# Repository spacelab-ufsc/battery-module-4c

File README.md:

<h1 align="center">
	BATTERY MODULE 4 CELLS
	<br>
</h1>

<h4 align="center">Electrical power system battery module 4 cells hardware project (sources, outputs, and documentation).</h4>

<p align="center">

</p>

<p align="center">
  	<a href="#overview">Overview</a> •
  	<a href="#architecture">Architecture</a> •
  	<a href="#interface">Interface</a> •
  	<a href="#version">Version</a> •
  	<a href="#license">License</a> •
  	<a href="#notes">Notes</a>
</p>

## Overview

## Architecture

## Interface

## Version

The current version of the project is v0.1, the status is ```development```.

## License

This project is licensed under CERN Open Hardware License, version 2.

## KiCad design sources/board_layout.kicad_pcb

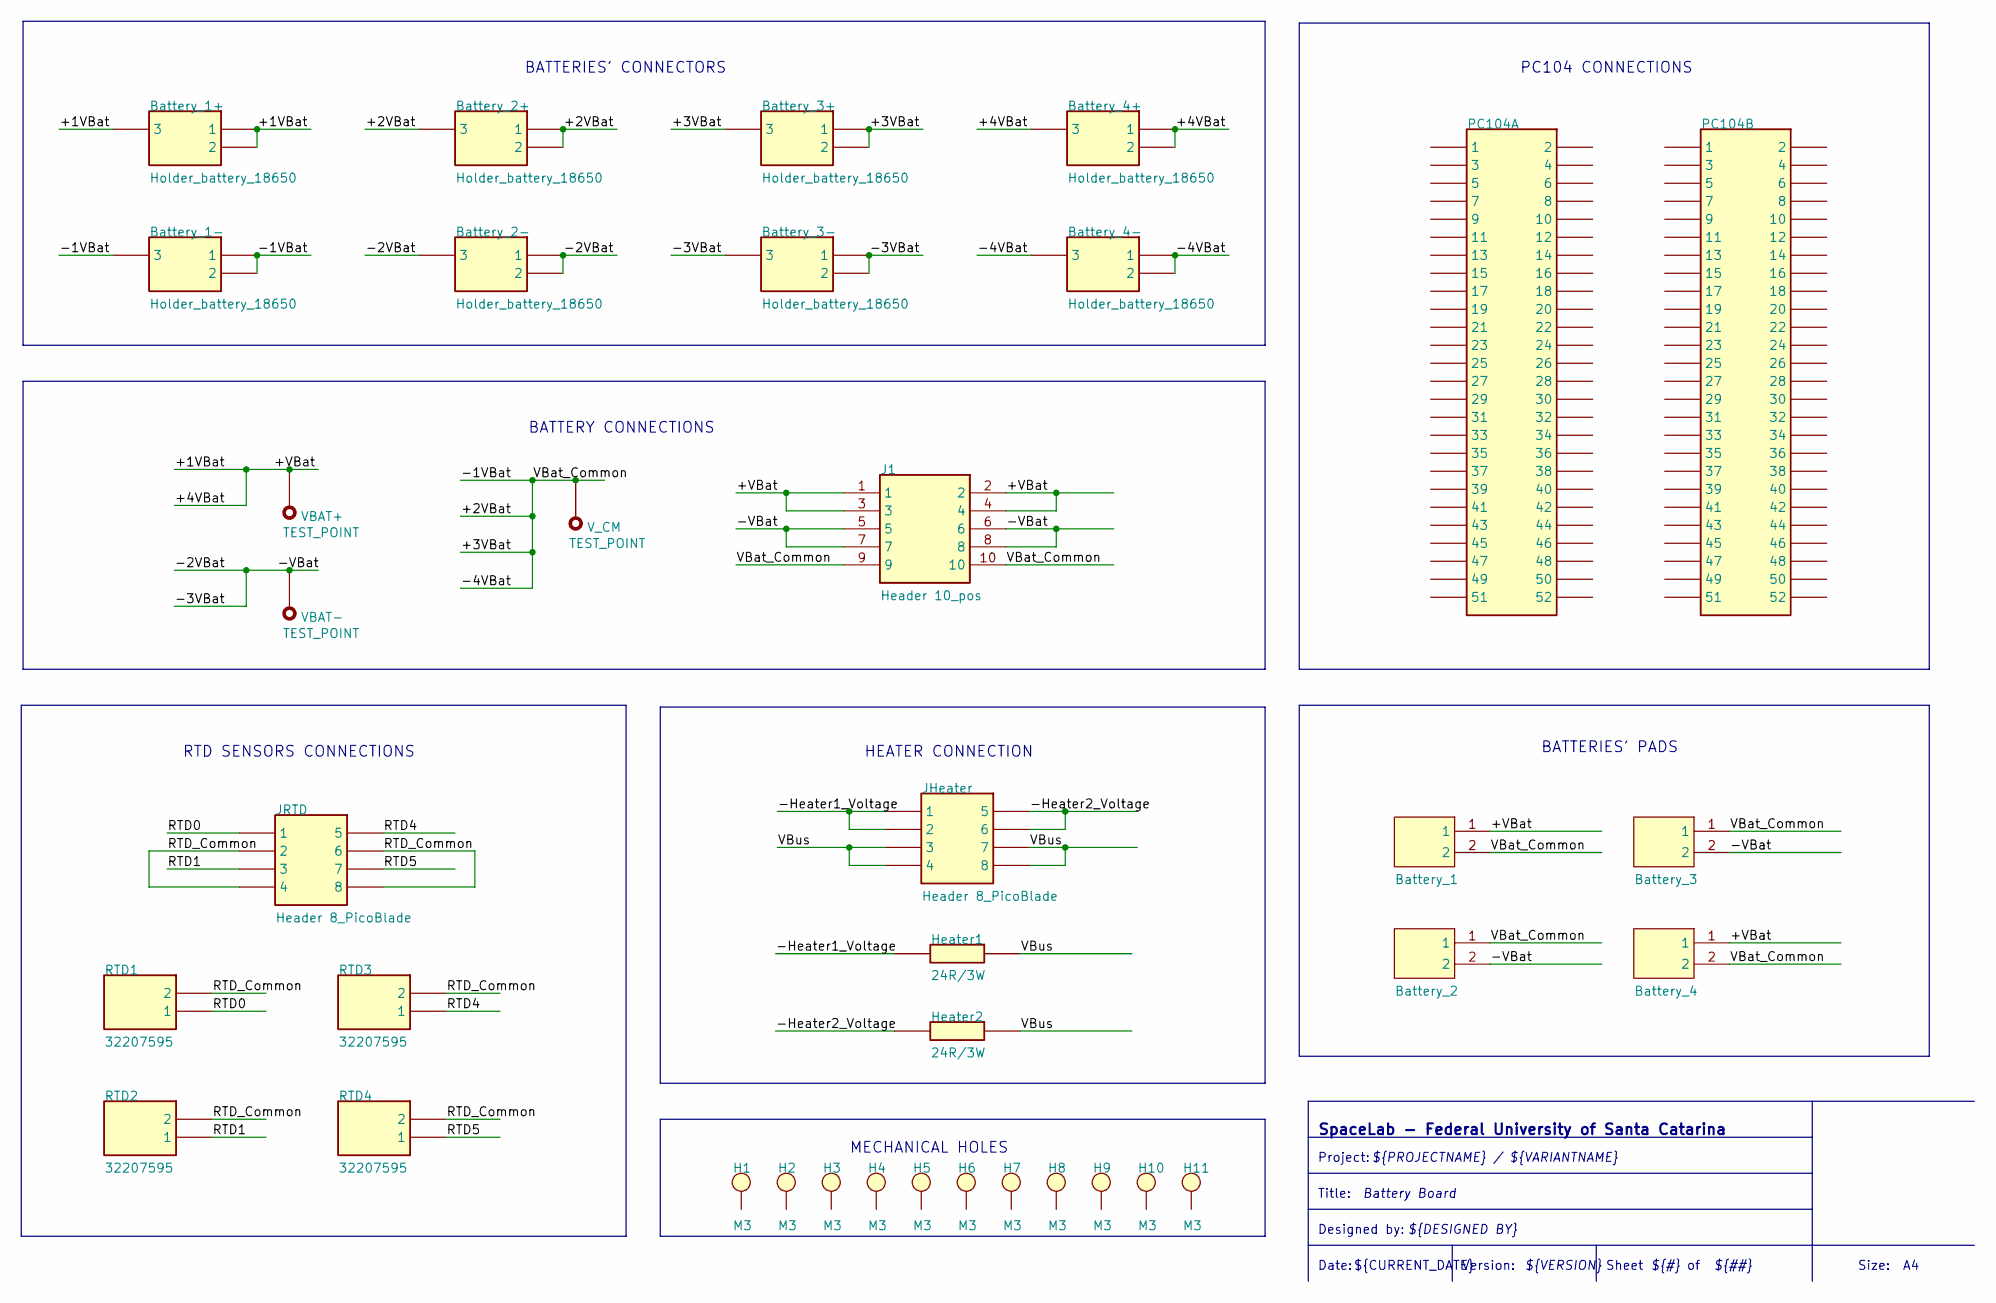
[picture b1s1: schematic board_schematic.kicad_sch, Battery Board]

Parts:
Battery_1, Battery_2, Battery_3, Battery_4: BATTERY
Battery_1+, Battery_1-, Battery_2+, Battery_2-, Battery_3+, Battery_3-, Battery_4+, Battery_4-: Holder_battery_18650; 54; MANUFACTURER_PART_NUMBER 54; MOUSER PART NUMBER 534-54
H1, H2, H3, H4, H5, H6, H7, H8, H9, H10, H11: M3; M3 hole
Heater1, Heater2: 24R/3W; RESAD3322W86L1422D475; MANUFACTURER_PART_NUMBER RS02B24R00FE12
J1: Header 10_pos; _Users_User_Desktop_Backup F__2020_Personal GitKraken_batte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; MANUFACTURER_PART_NUMBER 67996-110HLF; MOUSER PART NUMBER 649-67996-110HLF
JHeater: Header 8_PicoBlade; 53398-0871; MOUSER2 PART NUMBER 538-53398-0871
JRTD: Header 8_PicoBlade; 53398-0871; MOUSER2 PART NUMBER 538-53398-0871
PC104A, PC104B: ESQ-126-39-G-D; ESQ-126-Y-X-D; MANUFACTURER_PART_NUMBER ESQ-126-39-G-D; MOUSER PART NUMBER 200-ESQ12639GD
RTD1, RTD2, RTD3, RTD4: 32207595; THRMC3216X70N; MANUFACTURER_PART_NUMBER 32207595
VBAT+: TEST_POINT; Test_Point
VBAT-: TEST_POINT; Test_Point
V_CM: TEST_POINT; Test_Point

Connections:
+1VBat: Battery_1.1, Battery_1+.1, Battery_1+.2, Battery_1+.3, Battery_4.1, Battery_4+.1, Battery_4+.2, Battery_4+.3, J1.1, J1.2, J1.3, J1.4, VBAT+.1
+2VBat: Battery_1.2, Battery_1-.1, Battery_1-.2, Battery_1-.3, Battery_2.1, Battery_2+.1, Battery_2+.2, Battery_2+.3, Battery_3.1, Battery_3+.1, Battery_3+.2, Battery_3+.3, Battery_4.2, Battery_4-.1, Battery_4-.2, Battery_4-.3, J1.9, J1.10, V_CM.1
-2VBat: Battery_2.2, Battery_2-.1, Battery_2-.2, Battery_2-.3, Battery_3.2, Battery_3-.1, Battery_3-.2, Battery_3-.3, J1.5, J1.6, J1.7, J1.8, VBAT-.1
-Heater1_Voltage: Heater1.1, JHeater.1, JHeater.2
-Heater2_Voltage: Heater2.1, JHeater.5, JHeater.6
RTD0: JRTD.1, RTD1.1
RTD1: JRTD.3, RTD2.1
RTD4: JRTD.5, RTD3.1
RTD5: JRTD.7, RTD4.1
RTD_Common: JRTD.2, JRTD.4, JRTD.6, JRTD.8, RTD1.2, RTD2.2, RTD3.2, RTD4.2
VBus: Heater1.2, Heater2.2, JHeater.3, JHeater.4, JHeater.7, JHeater.8

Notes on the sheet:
SpaceLab - Federal University of Santa Catarina
BATTERIES' PADS
Size:
${CURRENT_DATE}
${##}
${DESIGNED BY}
${TITLE}
RTD SENSORS CONNECTIONS
BATTERIES' CONNECTORS
${PROJECTNAME} / ${VARIANTNAME}
BATTERY CONNECTIONS
Designed by:
Title:
PC104 CONNECTIONS
Version:
HEATER CONNECTION
${VERSION}
MECHANICAL HOLES
Date:
Project:
Sheet
${#}

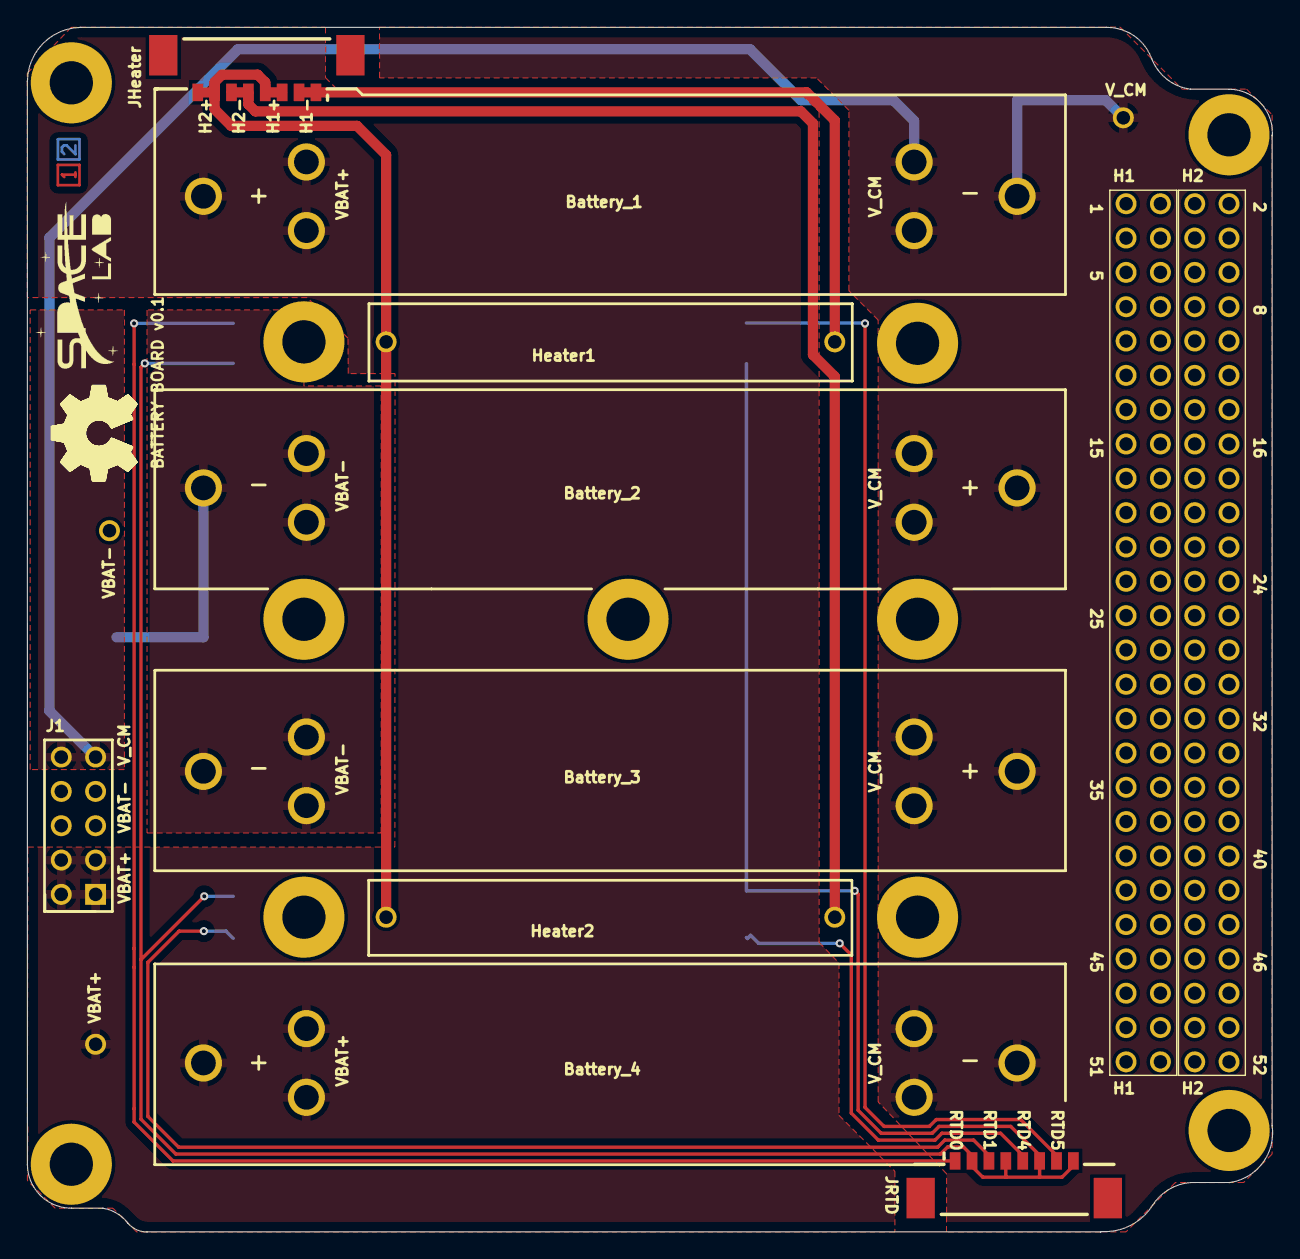
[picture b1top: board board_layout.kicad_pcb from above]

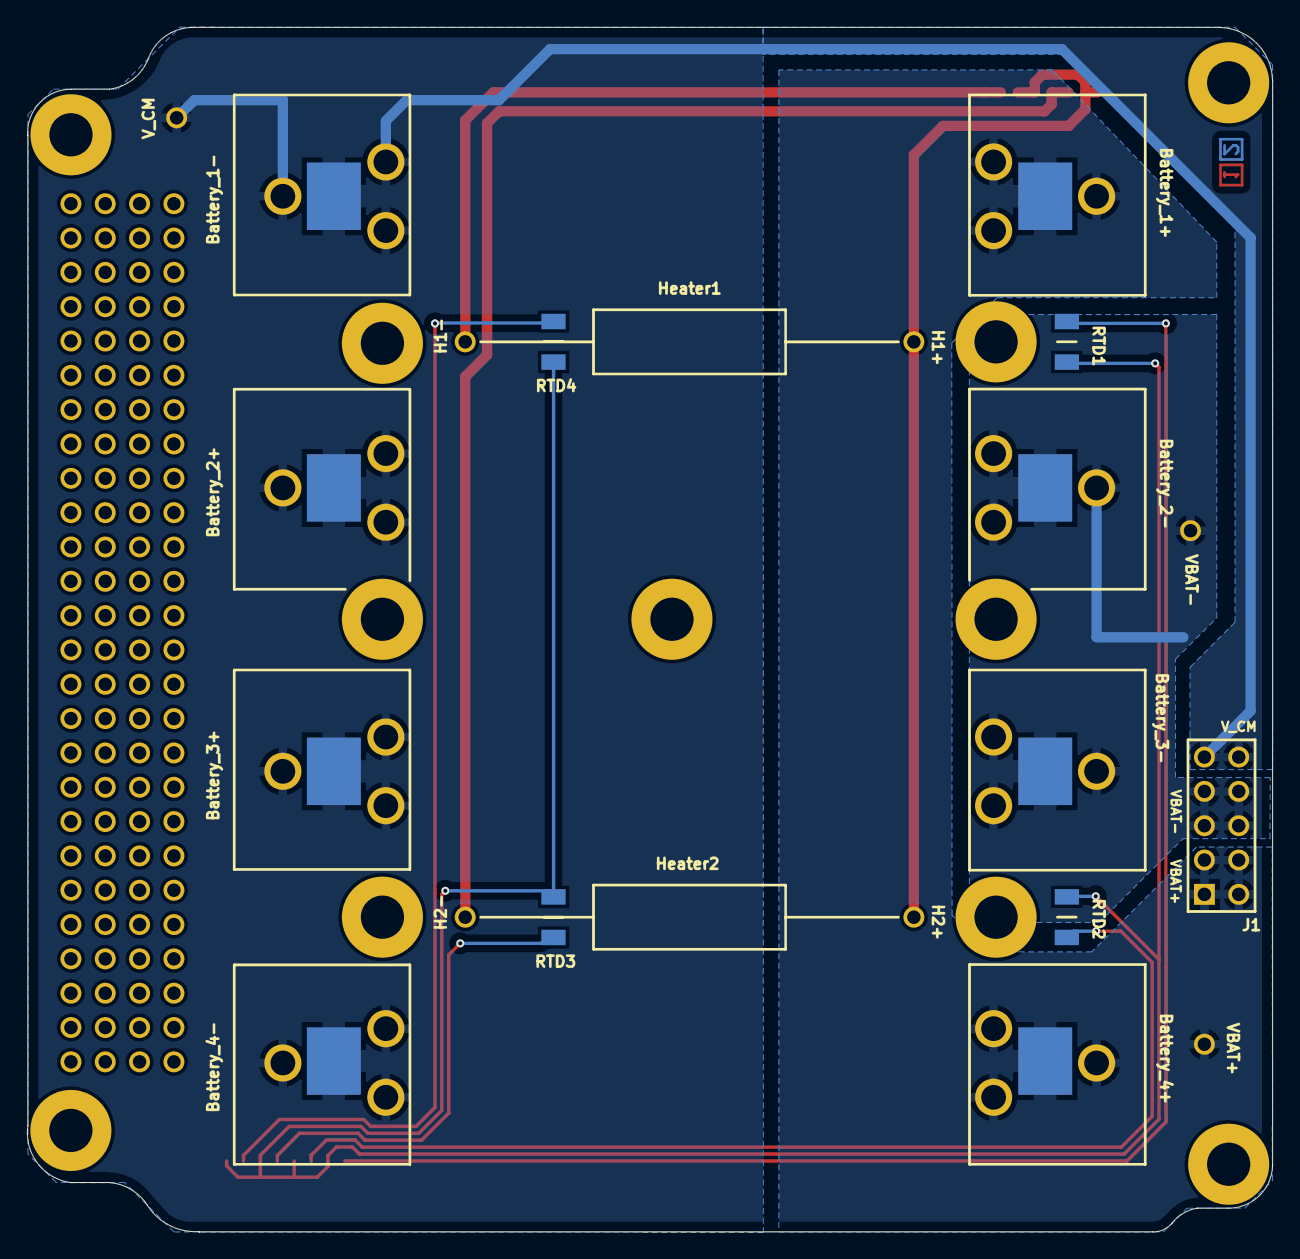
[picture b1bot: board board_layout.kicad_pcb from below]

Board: 2 copper layers, 92.1 x 89.1 mm, 37 parts (18 on the bottom side), 11 nets.

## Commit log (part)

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2020-05-06 hardware: Adding working files #1
2020-05-07 hardware: adding preliminary board shape and holes #2
2020-05-18 hardware: deleting resistors, adding step files, placing components #3
    Deleting resistors for replacement; additional step files of batteries, battery clips, preliminary resistors, PC104 connectors; placing first positioning of batteries, clips, sensors and resistors.
2020-05-27 hardware: replacing connectors and components, organizing files #4
    changing placement layers of picoblades, sensors, heaters and battery connectors; changing project files because of an minor error
2020-05-27 hardware: adding preliminary battery nets #5
    adding battery connectors polygon nets for posterior connection
2020-05-27 hardware: re-ranging heater's picoblade connections #6
    re-ranging net names for the heater's picoblade for compatibility with EPS board
2020-05-27 hardware: adding heater nets #8
2020-05-27 hardware: changing RTD's pins, removing pin numbers #7
    - rearranging RTD's picoblade pins for interface with EPS;
    - removing unnecessary information in the schematics.
2020-05-27 hardware: editing battery nets, changing sensors positions #9
    - connecting the battery clips nets to the J1 connector (EPS power connector);
    - removing sensors positions for future decision of them;
2020-05-27 hardware: arranging sensors positions, adding battery pads reference #10
    - placing new positions for the sensors, which was only possible by changing some of the battery nets;
    - adding a reference for future battery pads if the connectors aren't needed
2020-05-28 hardware: changing RTD's positions, connecting nets #11
    - changing RTD 2 and 4 position for better placement of the nets;
    - connecting the nets onto the RTD's picoblade.
2020-06-02 hardware: editing and replacing nets and vias #12
    - changes in heater's nets width and placement
    - changes in the rtd's nets and vias width
    - replacing rtd's nets for better positioning
2020-06-21 hardware: adding libraries and creating testpoint #13
    - creating a schematic and a PCB library
    - creating a testpoint symbol for the schematic
    - adding the testpoint footprint
2020-06-21 hardware: changing connections in the sheet #14
    - changing connectors' wires for better visualization
2020-06-21 hardware: adding testpoints to the sheet #15
    - placing the testpoints in the power connections
2020-06-21 hardware: netting testpoints #17
2020-06-21 hardware: adding and placing testpoints in the PCB #16
    - updating sheet connections to the PCB
    - placing testpoints far from battery clips, but near original nets
2020-06-24 hardware: creating battery direct pads #18
2020-06-24 hardware: creating battery's schematic symbol #19
2020-06-24 hardware: adding the new battery symbols to the schematic #20
2020-06-24 hardware: updating battery's files #21
2020-06-25 hardware: updating battery symbols to the schematic #22
2020-06-25 hardware: placing battery pads into the PCB #23
2020-06-27 hardware: editing polygon connections #24
2020-06-27 hardware: rearranging silkscreen #25
2020-06-27 hardware: minor silkscreen updates #26
2020-06-28 hardware: placing drill holes #27
2020-06-28 Ignoring all preview files from the project
2020-06-28 hardware: adding logo and board's name #28
    - minor labeling changes
    - adding FloripaSat's logo and board's name to the PCB project
    - final version of V2.0
2020-06-28 hardware: updating list of components on the libraries #29
2020-06-28 documentation: updating template's patch #2
2020-06-28 documentation: updating patch's placement #3
2020-07-02 hardware: updating schematics #30
    - deleting different common paths and combining them to a single one
2020-07-02 hardware: updating PCB after schematic changes #31
    - connecting all commons and deleting extra testpoint
    - aligning drill holes
2020-07-02 hardware: updating silkscreen #32
2020-07-11 documentation: updating patch's placement #4
    obs: after merge, update patch's location on the project
2020-07-11 documentation: creating pdf file for schematic #5
2020-08-17 hardware: minor changes in the silkscreen, adding GOLDS patch #32
    Also minor changes in the schematic template.
2020-08-18 documentation: updating schematics' pdf and adding project's BOM #6
    - rewriting component descriptions and names
    - adding an excel file with list of components
    - adding a pdf file of the same list
2020-08-18 hardware: updating project, adding used 3D step files #34
    - minor changes such as linking the footprints to the libraries
    - adding battery, battery clips and PC104 step files
2020-08-18 hardware: adding gerbers and drill files #35
2020-09-15 Fabrication: Generating preliminary fabrication files
2020-09-28 hardware: schematics: Updating sheet template and adding mechanical holes
2020-09-28 hardware: layout: Adding mechanical holes and power copper polygons
2020-09-29 hardware: layout: Updating logos, render color and board name
2020-09-29 hardware: libraries: Updating power header footprint and 3D model
2020-09-29 hardware: layout: Fixing DRC non-critical errors
2020-09-29 hardware: layout: Adding sheet template, layer names, dimensions and fabrication info
2020-09-29 hardware: layout: Updating sheet header information
2020-09-29 hardware: Updating folders structure and refactoring nomenclature. close #8
2020-09-29 hardware: outputs: Adding all fabrication, output and documentation files
2020-09-29 hardware: outputs: Updating output and fabrication files
2020-09-29 hardware: images: Adding pcb 3d images
2020-10-02 hardware: outputs: board_bom: Updating BOM manually using SpaceLab template close #5
2020-10-03 hardware: outputs: board_bom: Swaping manually the picoblade vertical component to the right angle version #5
2020-10-04 hardware: outputs: Removing old outputs and documentation
2020-10-04 hardware: libraries: Removing old libraries
2020-10-04 hardware: libraries: Adding updated libraries
2020-10-04 readme: Updating top flags and content
2020-10-04 Changing the license to CERN OHL v2 #11
2020-10-17 Updating the main README file
2020-11-07 Removing the Altium outputs from the documentation branch
2020-11-07 Importing the LaTeX template. closes #14
2021-01-20 documentation: Adding new SpaceLab 2021 logo image and deleting old one #18
2021-01-20 documentation: header: Updating SpaceLab logo close #18
2021-01-22 hardware: sources: Adding 0_architecture schematic with version control table, project information and simple block diagram close #19
2021-01-22 hardware: sources: Updating main schematic with SpaceLab template
2021-01-22 hardware: images: adding dummy block diagram PNG image and editable drawio file
2021-01-22 hardware: Updating project file with new architecture schematic and parameters (name of the board designer, revision and project code)
2021-01-22 hardware: outputs: board_schematics: Updating both reduced and full schematics with new schematic and sheet template
2021-01-22 hardware: images: Fixing the transparent background and name of the block diagram images
2021-01-22 hardware: libraries: Updating picoblade connector with the right-angle version and minor fixes to components comments
2021-01-22 hardware: sources: Updating picoblade connector with the right-angle version on schematic and pcb documment
2021-01-22 hardware: images: Updating pcb 3d and top images with new picoblade right angle and SpaceLab 2021 logo
2021-01-22 hardware: Fixing project code parameter #20
2021-01-22 hardware: outputs: board_prints and board_schematics: Updating pdfs with new project code and right angle PicoBlade connector close #20
2021-01-25 doc: references: Adding BAT4C, EPS2 repositories and the first battery board 1.0 wiki page reference
2021-01-25 doc: chapters: Adding BAT4C, EPS2 repositories and the first battery board 1.0 wiki page reference
2021-01-25 doc: chapters: Adding initial version of the introduction chapter close #21
2021-02-04 doc: header: Updating dates and including v0.2 to revision control table
2021-02-04 doc: figures: Adding basic block diagram png and editable file
2021-02-04 doc: Adding initial system overview chapter close #22
2021-02-09 doc: Fixing the title page according to the document template
2021-02-14 doc: figures: Adding images for the hardware chapter #23
2021-02-14 doc: references: Adding temperature sensor (RTD) datasheet reference
2021-02-14 doc: chapters: Adding initial version of the hardware chapter #23
2021-03-09 Hardware: libraries: schematic_library and footprints_library: Upload components and footprints for the battery management system
2021-04-01 hardware: sources: Add Battery_management_system.schdoc - hardware: libraries: Update schematics and footprints libraries
2021-04-04 hardware: sources: Update schematics of bms #26
2021-04-04 hardware: sources: BMS schematic Updated hardware: libraries: schematic and footprint libraries updated
2021-04-05 hardware: sources: BMS schematic updated #26 hardware: libraries: schematic and footprint libraries updated
2021-04-05 hardware: fix project structure error
2021-04-17 hardware: sources: Updating SpaceLab logo on sheet layer and changing imperial units to metric in drill and stack up table
2021-05-25 hardware: sources: Renaming schematic for the new battery manager IC #26
2021-05-25 hardware: libraries: Improving/fixing some schematic and footprint components
2021-05-25 hardware: sources: Removing the 54 battery contacts and lower pads from schematic and adding strip pads #32
2021-05-25 hardware: sources: Renaming main schematic for interfaces
2021-05-25 hardware: sources: Preliminary positioning strip pads, mouting holes for mechanical case and picoblades #4 #29 #32
2021-05-25 hardware: Updating project file tree and removing room generating during ECO
2021-06-08 hardware: libraries: Improving Batteries, mouting holes for mechanical case and CSD16412Q5A symbols and footprints #28
2021-06-15 hardware: sources: Updating license to CERN-OHL-S version 2 and adding description of v0.2 release
2021-06-15 hardware: sources: interface: Removing PC104 interface, improving battery symbol, removing 2 RTDs leaving 4 free pins on picoblade for new interfaces and adding mechanical case mouting holes #34
2021-06-15 hardware: sources: board_layout: Repositioning batteries near heaters, including new mechanical case mouting holes, removing the PC104 interface close #34
2021-06-15 hardware: libraries: Minor fixes to mechanical case mouting holes and batteries footprints
2021-06-15 hardware: sources: board_layout: Finished routing, DRC pending
2021-06-15 hardware: sources: Improving track distances of still 2-wire rtd configuration, adding -vbat (gnd) polygon plane to top layer
2021-06-16 hardware: sources: Updating revision history description and date, updating picoblade interface with GPIOs that can be used in future release
2021-06-16 hardware: sources: layout: Updating picoblade interface, tenting vias, adding teardrops, adding middle RTD component, fixing sheet information
2021-06-16 hardware: sources: layout: Increasing battery pad connection thickness, fixing DRC error from picoblade silkcreen on solder mask opening, increasing cleareance from polygons to tracks and vias
2021-06-16 hardware: fabrication: Updating gerber_ncdrills zip, pick_place and adding BOM #38
2021-06-16 hardware: libraries: Fixing partnumber parameter name for some components hardware: sources: Updating component parameters in schematic and layout
2021-06-16 hardware: sources: layout: Fixing Mechanical 13 and 15 layer names to ASM bottom and ASM top
2021-06-16 hardware: libraries: Adding ASM top and bottom layers hardware sources: Updating components with new ASM top and bottom marks
2021-06-16 hardware: outputs: board_schematics: Adding updated schematics to v0.2 #38
2021-06-16 hardware: outputs: board_prints: Updating board prints v0.2 #38
2021-06-16 hardware: sources: Fixing picoblade silkcreen labels and missing test point label
2021-06-16 hardware: Updating gerber_ncdrills zip, board prints and full pdf with fixed silkscreen labels on picoblades #38
2021-07-03 doc: Preparing v0.2 release #40
2021-07-05 hardware: outputs: Updating all outputs files for v0.2 #40 close #38
2021-07-05 hardware: outputs: Removing individual gerber files from repo #40

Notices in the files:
README.md:
License: CERN OHL 2
